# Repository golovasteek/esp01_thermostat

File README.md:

# Smart Thermostat based on ESP-01 board

The software to run on the thermostat to control temperature in the
room with a floor heating.

The target board is ESP-01, but it should be possible to run it on
any ESP8266 board.

The project uses DS18b20 as temperature sensors

GPIO 2 is used to connect with senosor
GPIO 0 is used to control relay, relay is supposed to be active low.

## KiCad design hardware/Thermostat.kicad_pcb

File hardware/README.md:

# Hardware design of the thermostat

## Tools

The hardware design is made in KiCAD version 5

You can view it on [CADLAB.io](https://cadlab.io/project/25945).

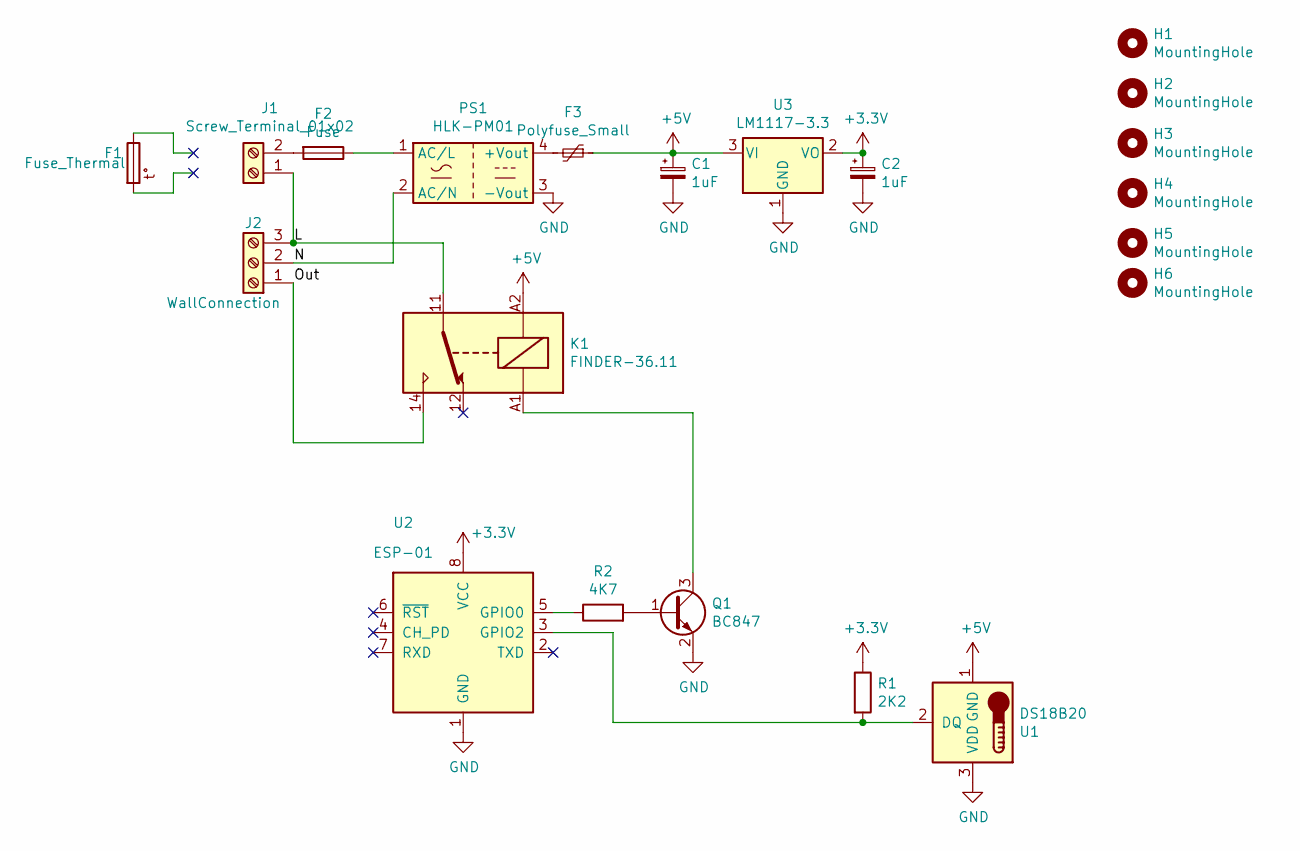
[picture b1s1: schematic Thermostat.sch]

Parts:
C1, C2: 1uF; CP_EIA-3528-12_Kemet-T_Pad1.50x2.35mm_HandSolder
F1: Fuse_Thermal
F2: Fuse; Fuseholder_Clip_5x20_ESKA
F3: Polyfuse_Small; Fuse_Bourns_MF-RG500
H1, H2: MountingHole; MountingHole_6mm
H3, H4, H5, H6: MountingHole; MountingHole_3.2mm_M3
J1: Screw_Terminal_01x02; TerminalBlock_RND_205-00232_1x02_P5.08mm_Horizontal
J2: WallConnection; TerminalBlock_RND_205-00233_1x03_P5.08mm_Horizontal
K1: FINDER-36.11; Relay_SPDT_Finder_36.11
PS1: HLK-PM01; Converter_ACDC_HiLink_HLK-PMxx
Q1: BC847; SOT-23
R1: 2K2; R_0805_2012Metric_Pad1.20x1.40mm_HandSolder
R2: 4K7; R_0805_2012Metric_Pad1.20x1.40mm_HandSolder
U1: DS18B20; TO-92_Inline
U2: ESP-01; Samtec_HLE-104-02-xx-DV-TE_2x04_P2.54mm_Horizontal
U3: LM1117-3.3; TO-252-3_TabPin2

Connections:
+3V3: C2.1, R1.1, U2.8 (VCC), U3.2 (VO)
+5V: C1.1, F3.1, K1.A2, U1.1 (GND), U3.3 (VI)
/L: J1.1, J2.3, K1.11
/N: J2.2, PS1.2 (AC/N)
/Out: J2.1, K1.14
GND: C1.2, C2.2, PS1.3 (-Vout), Q1.2 (E), U1.3 (VDD), U2.1 (GND), U3.1 (GND)
unnamed: F2.1, PS1.1 (AC/L)
unnamed: F2.2, J1.2
unnamed: F3.2, PS1.4 (+Vout)
unnamed: K1.A1, Q1.3 (C)
unnamed: Q1.1 (B), R2.2
unnamed: R1.2, U1.2 (DQ), U2.3 (GPIO2)
unnamed: R2.1, U2.5 (GPIO0)

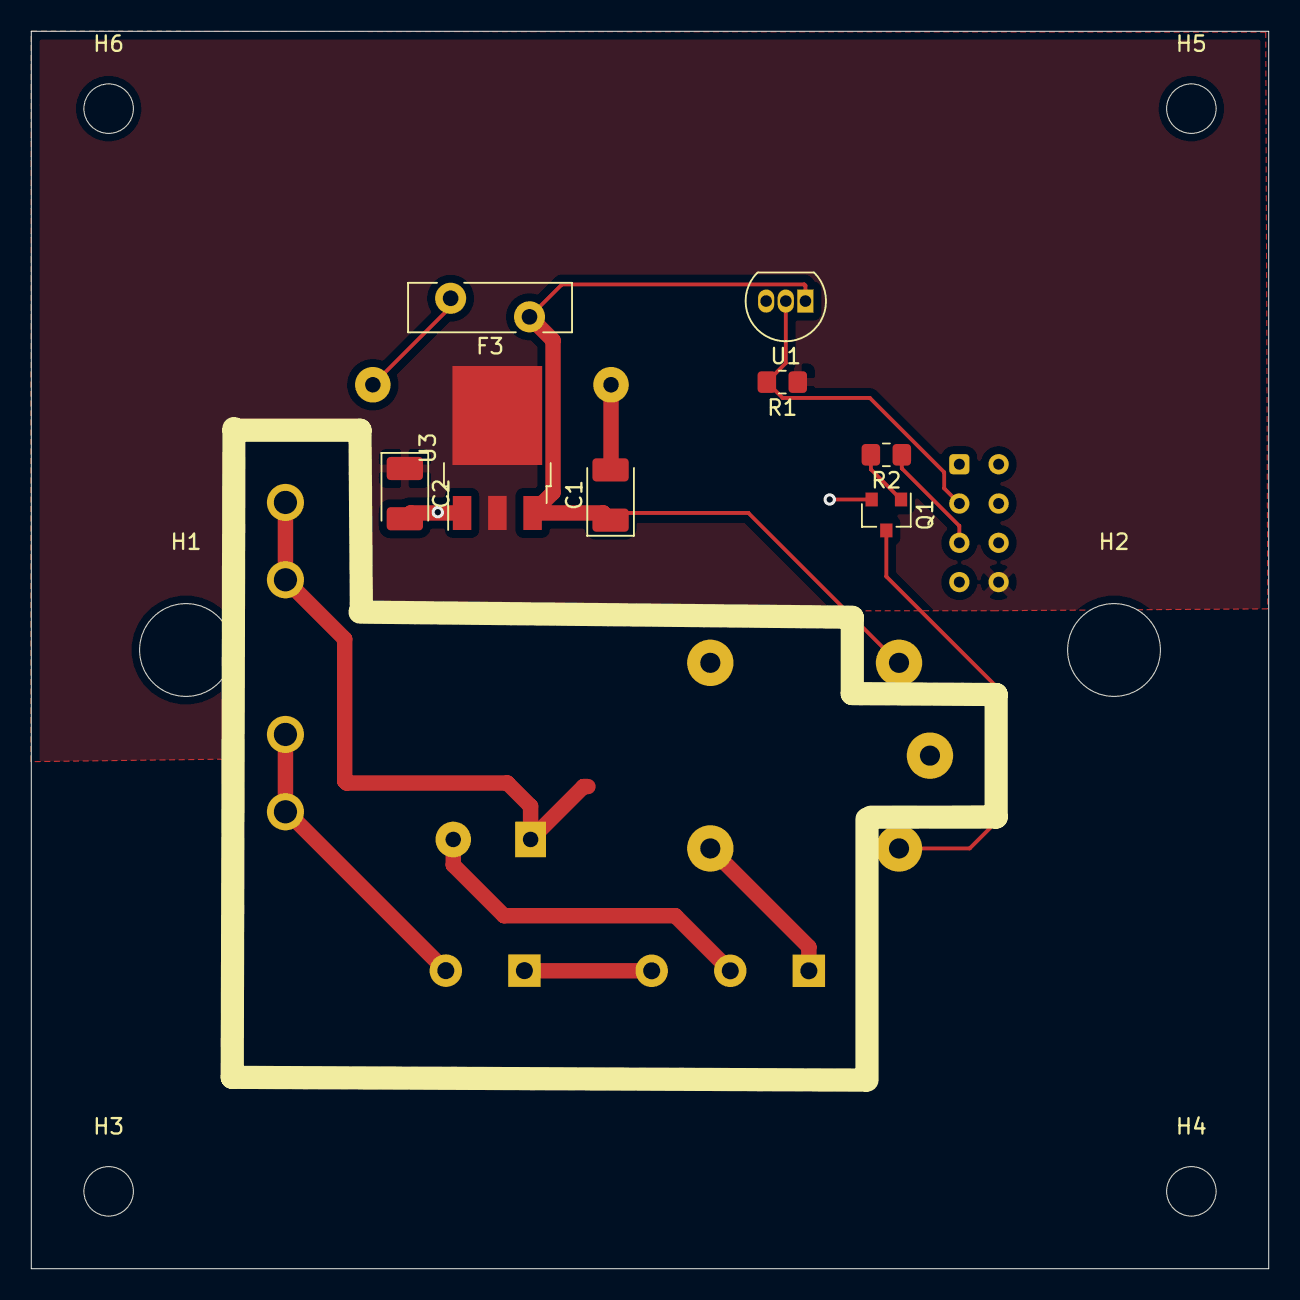
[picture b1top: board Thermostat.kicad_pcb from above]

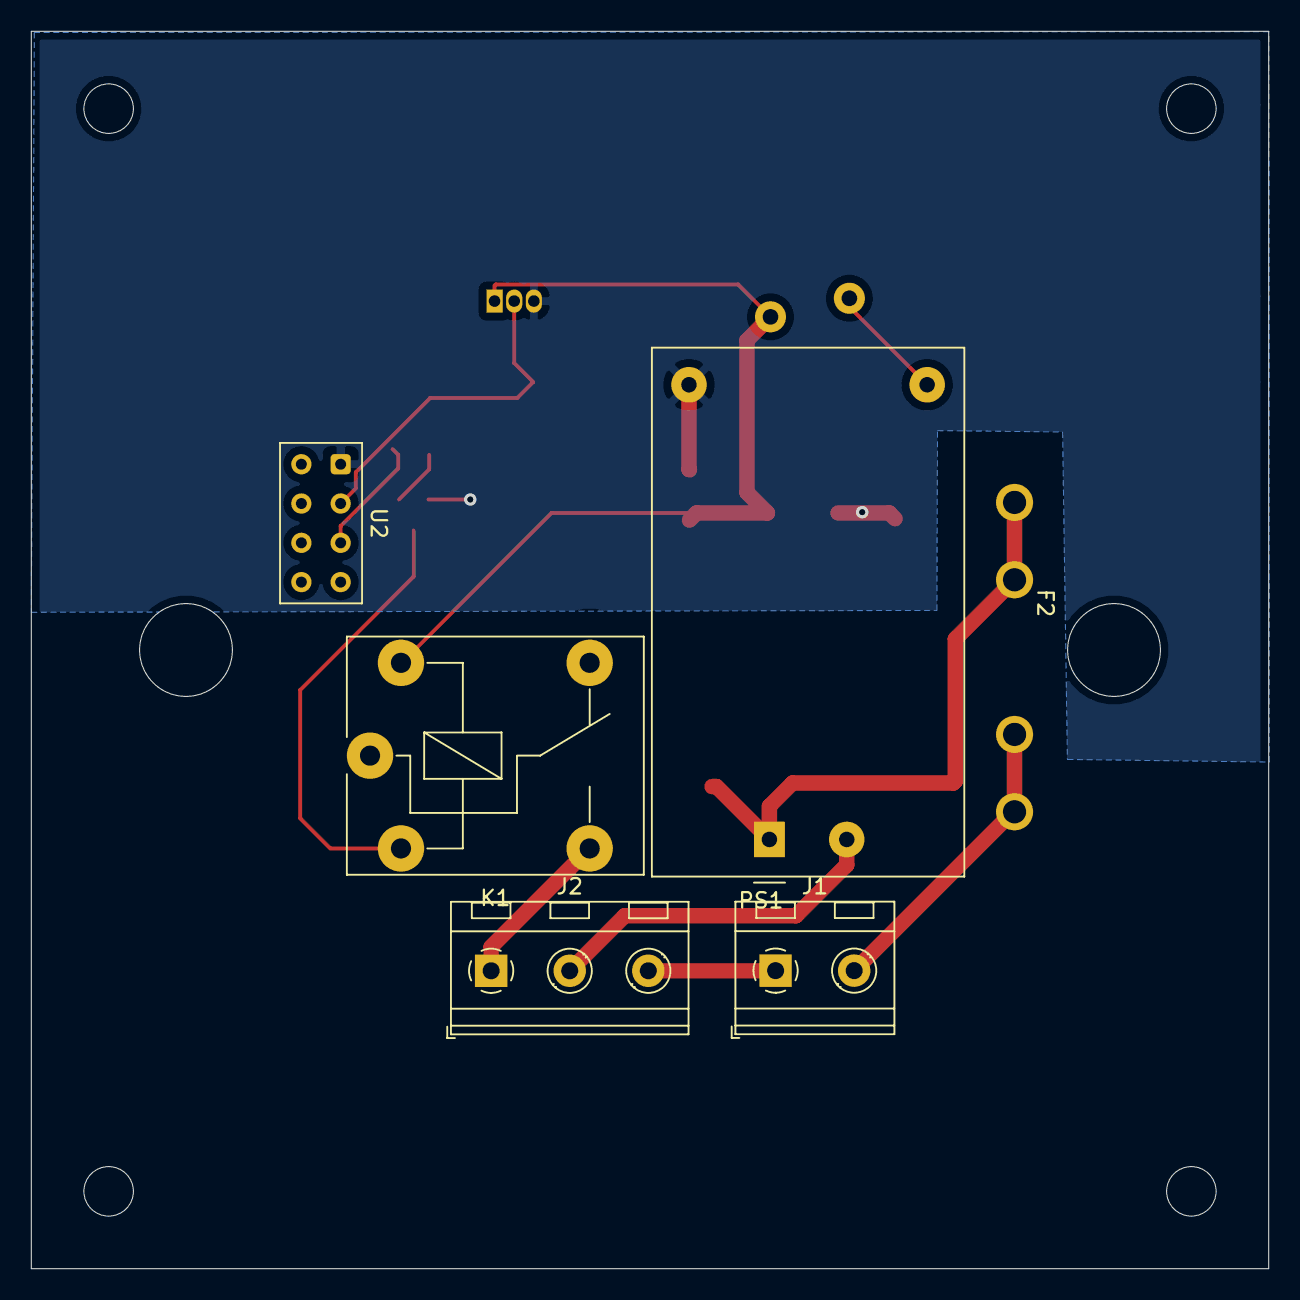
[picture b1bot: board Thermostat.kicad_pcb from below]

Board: 2 copper layers, 80.0 x 80.0 mm, 20 parts (6 on the bottom side), 13 nets.

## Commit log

2022-09-11 Support for AWS IoT core, refactoring, no Blynk anymore
2022-09-11 add readme
2022-09-11 Add a picture
2022-09-11 Reduce Image size
2022-09-11 Add hardware design
2022-09-11 Backlink to CADLAB.io has been added.
2022-09-11 Add README for hardware
2022-09-11 Add cache.lib file
